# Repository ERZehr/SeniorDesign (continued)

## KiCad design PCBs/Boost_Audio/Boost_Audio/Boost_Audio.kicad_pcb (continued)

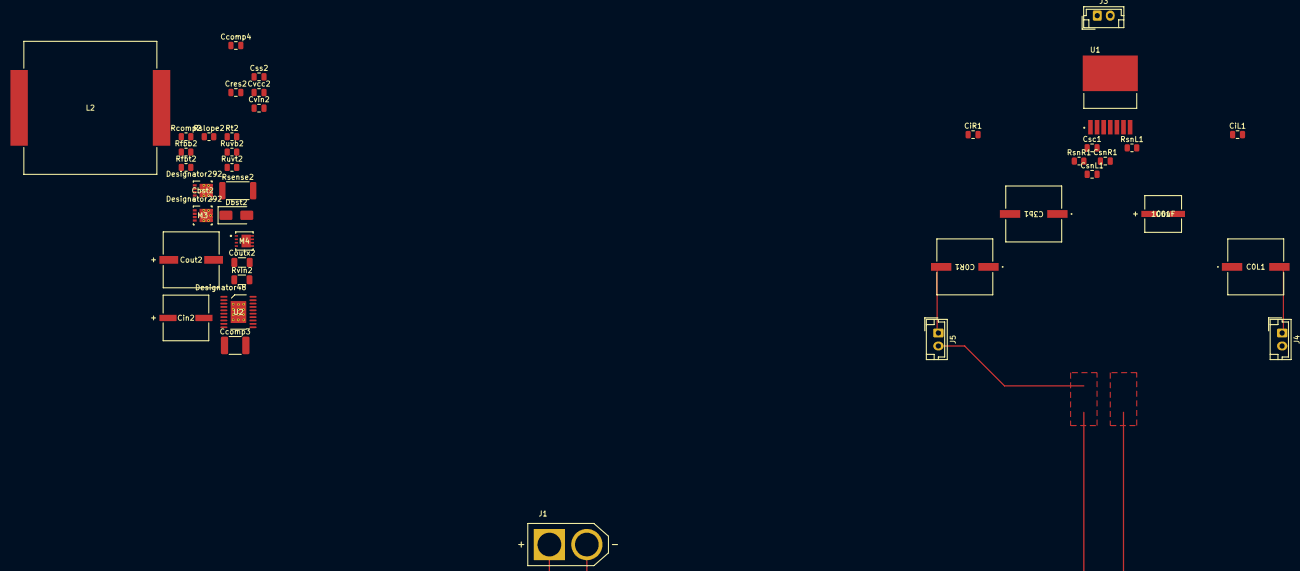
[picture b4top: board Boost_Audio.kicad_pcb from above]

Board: 2 copper layers, 40 parts (0 on the bottom side), 30 nets.

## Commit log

2024-01-19 original repo setup
2024-01-19 added external_libs folder
2024-01-19 Add files via upload
    Drawings and system overview
2024-01-19 Add files via upload
    Changed BLE -> Bluetooth
2024-01-19 added assignments folder
2024-01-21 Added voltage regulation and light sensor circuit diagrams
2024-01-21 Added converters duty cycle setup file
2024-02-07 editing power module
2024-02-13 ESP-IDF Example Code
2024-02-13 Create blank
2024-02-13 ESP-IDF Examples
2024-02-13 Create esp32
2024-02-13 added PCBs
2024-02-14 new decoupling cap
2024-02-14 updated PCB main
2024-02-15 latest PCBs
2024-02-16 PCB combination
2024-02-16 PCB, LED pins and light sensor pins added
2024-02-16 merged into one PCB
2024-02-19 UART pins
2024-02-19 Corrected UART receive and transmit pins
2024-02-19 BOOT
2024-02-20 finished schematic
2024-02-21 finished Schematic spread PCB compnets for footprint compare
2024-02-21 started PCB Layout
2024-02-21 PCB reset traces
2024-02-21 fixed footprints
2024-02-21 added archives
2024-02-21 added pretty folder
2024-02-21 fixed
2024-02-23 Compatible with ESP-IDF BT code
2024-02-26 pcb almost done
2024-02-27 updates to PCB
2024-02-28 PCB no errors, added PCB sandbox
2024-02-28 Finished PCB sandbox design and added gbr and drl files
2024-02-28 fixed PCB layout and updated gbr and drl files
2024-02-28 fixed trace
2024-03-02 Arduino-Based - cut bloat and unnecessary patterns
2024-03-04 added final design files (not complete)
2024-03-05 finished Main and Light Sensor PCBs
2024-03-05 GRB and DRL added
2024-03-05 VSCode LED Matrix Code
2024-03-06 New audio amplifier PCB
2024-03-06 fixed board outline and generated new GBR and DRL files
2024-03-06 fixed vias and expanded boost converter
2024-03-06 WDT Fixed - FlowField Fixed
2024-03-07 Bloat removal
2024-03-20 README update, remove demo files
2024-03-20 WROOM_Code Initial Commit, build delete in LED_Matrix
2024-03-21 Initial WROOM Commit
2024-03-21 Successful Test
2024-03-24 Initial commit - needs work
2024-03-25 WROOM Build Fix, bad DSP code
2024-03-25 WROOM build fix, WROVER broken DSP still
2024-03-26 Analog read update - runs on PCB
2024-03-27 BT_DSP_THREAD general idea - bad build
2024-03-28 Brightness done, BT/DSP needs work
2024-03-28 README
2024-03-28 Brightness tweak
2024-04-02 One-filter BT/DSP
2024-04-02 README Update
2024-04-02 README changes, initial UART commit - doesn't work yet
2024-04-04 BLE Advertising Fix, WROVER DSP testing
2024-04-04 Initial UART - tested
2024-04-04 UART done for both WROOM and WROVER
2024-04-04 UART edited 30 HZ max, DSP in progress
2024-04-04 Temp if(true) fix
2024-04-06 Equalizer pattern, DSP still in progress
2024-04-06 Band logic fixed - need accurate constants. DSP needs work
2024-04-07 Create a
2024-04-09 DSP done, audio good - disp needs work
2024-04-10 Final micro project folders
2024-04-10 DSP Coefficient testing
2024-04-11 BT_DSP_2 has FFT, WROOM and WROVER updated accurately
2024-04-12 WROVER fixed
2024-04-15 WROVER Init coeffs, WROOM bars
2024-04-16 Build deletion
2024-04-16 Final FIR code
2024-04-16 Final code - needs cleaned
2024-04-17 Final comments and bloat removal
2024-04-19 WROOM TX Pin Change
2024-04-20 Software cleanup
2024-04-20 Submodule fix?
2024-04-20 Submodule fix, README update
2024-04-20 Bump cryptography
    Bumps [cryptography](https://github.com/pyca/cryptography) from 36.0.0 to 42.0.4.
    - [Changelog](https://github.com/pyca/cryptography/blob/main/CHANGELOG.rst)
    - [Commits](https://github.com/pyca/cryptography/compare/36.0.0...42.0.4)
    ---
    updated-dependencies:
    - dependency-name: cryptography
2024-04-20 Security fix broke build
2024-04-20 Security fix, good build
2024-04-22 removed fluff and deleted updated PCB directory
2024-04-22 Logo update, RX/TX update
2024-04-23 Final code uploaded
2024-04-23 Default to idle mode
2024-04-24 Final code comments and cleanup
2024-04-25 Updated Mobile App code to current
